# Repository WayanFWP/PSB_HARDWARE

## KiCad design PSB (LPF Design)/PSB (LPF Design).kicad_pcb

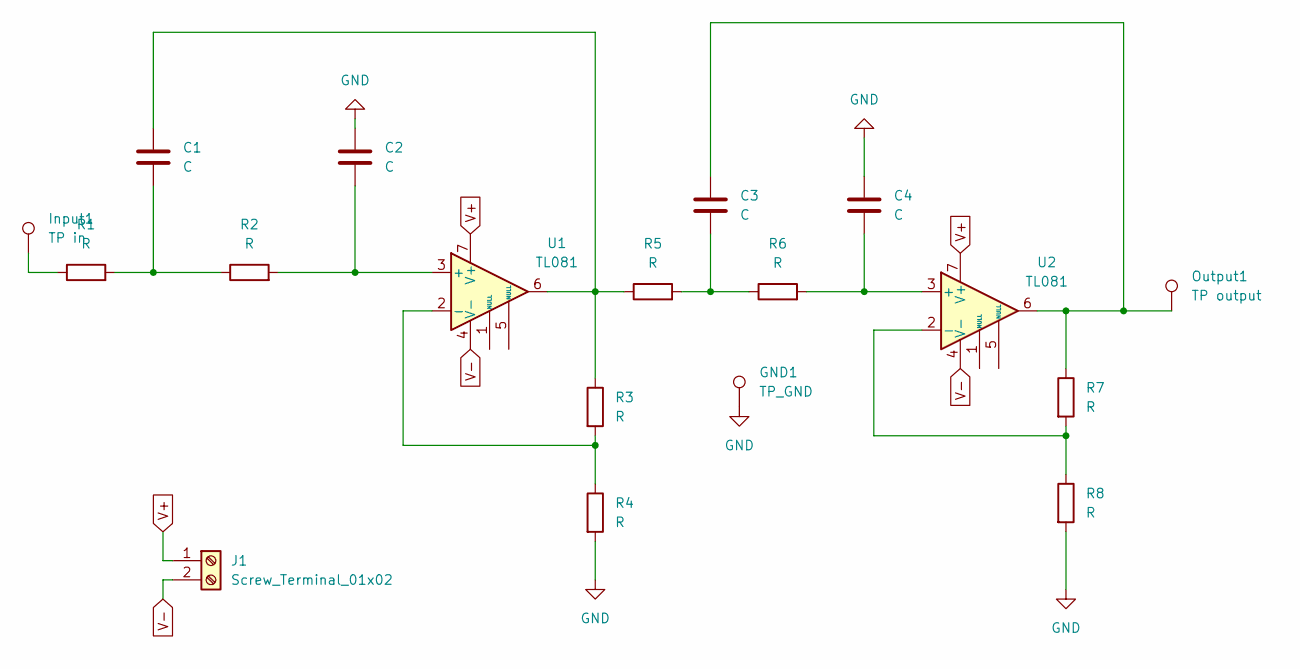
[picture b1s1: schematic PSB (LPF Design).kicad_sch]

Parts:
C1, C2, C3, C4: C; C_Disc_D5.0mm_W2.5mm_P2.50mm
GND1: TP_GND; Pin_D1.3mm_L11.0mm
Input1: TP in; Pin_D1.3mm_L11.0mm
J1: Screw_Terminal_01x02; TerminalBlock_MetzConnect_Type059_RT06302HBWC_1x02_P3.50mm_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
Output1: TP output; Pin_D1.3mm_L11.0mm
R1, R2, R3, R4, R5, R6, R7, R8: R; R_Axial_DIN0207_L6.3mm_D2.5mm_P7.62mm_Horizontal
U1, U2: TL081; DIP-8_W7.62mm_Socket

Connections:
GND: C2.1, C4.1, GND1.1, R4.2, R8.2
unnamed: C1.1, R3.1, R5.1, U1.6
unnamed: C1.2, R1.2, R2.1
unnamed: C3.1, Output1.1, R7.1, U2.6
unnamed: C3.2, R5.2, R6.1
unnamed: Input1.1, R1.1
unnamed: C2.2, R2.2, U1.3 (+)
unnamed: R3.2, R4.1, U1.2 (-)
unnamed: C4.2, R6.2, U2.3 (+)
unnamed: R7.2, R8.1, U2.2 (-)
V+: J1.1, U1.7 (V+), U2.7 (V+); also elsewhere on the board
V-: J1.2, U1.4 (V-), U2.4 (V-); also elsewhere on the board

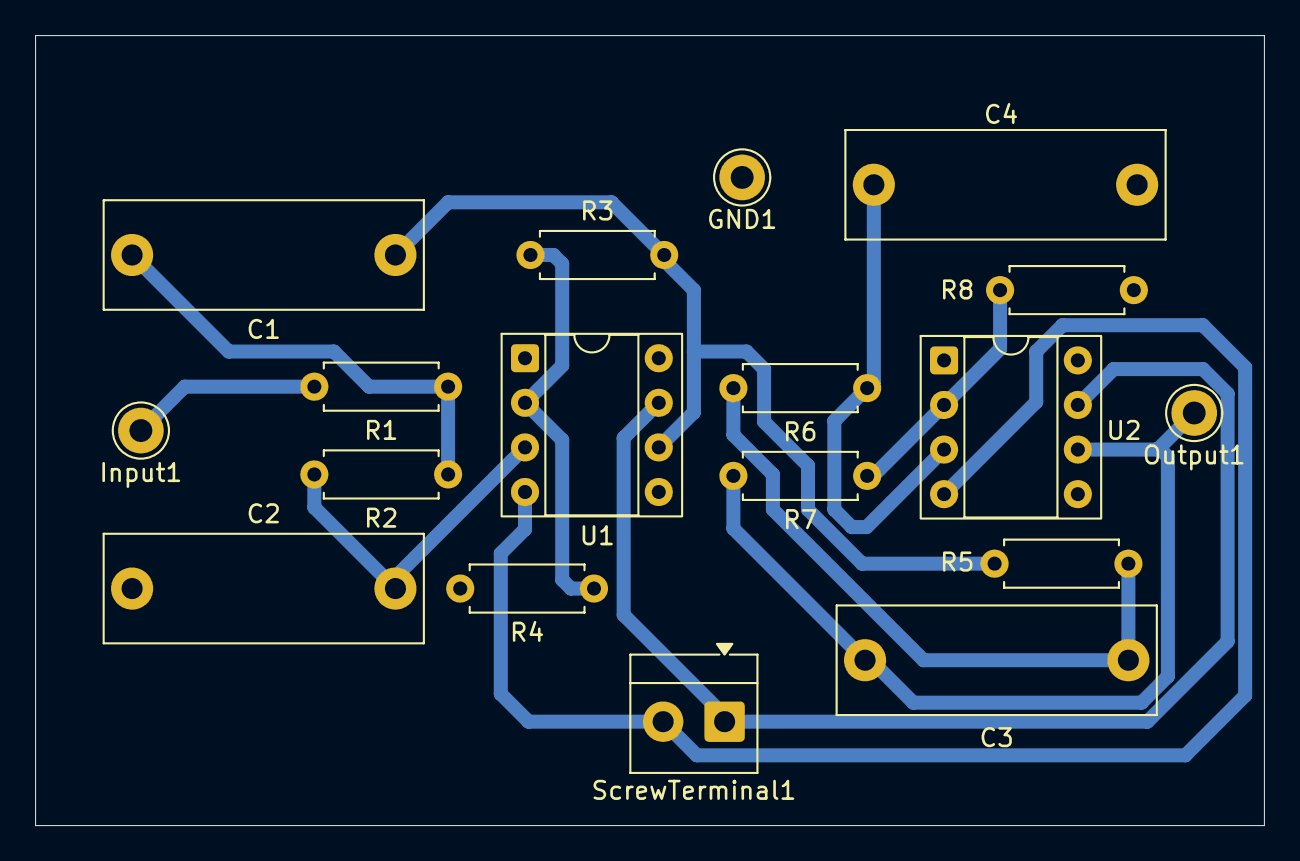
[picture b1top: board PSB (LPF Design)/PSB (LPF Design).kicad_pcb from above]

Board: 2 copper layers, 70.0 x 45.0 mm, 18 parts (0 on the bottom side), 12 nets.

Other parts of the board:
ScrewTerminal1: Screw_Terminal_01x02; TerminalBlock_MetzConnect_Type059_RT06302HBWC_1x02_P3.50mm_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

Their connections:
V+: ScrewTerminal1.1; also elsewhere on the board
V-: ScrewTerminal1.2; also elsewhere on the board

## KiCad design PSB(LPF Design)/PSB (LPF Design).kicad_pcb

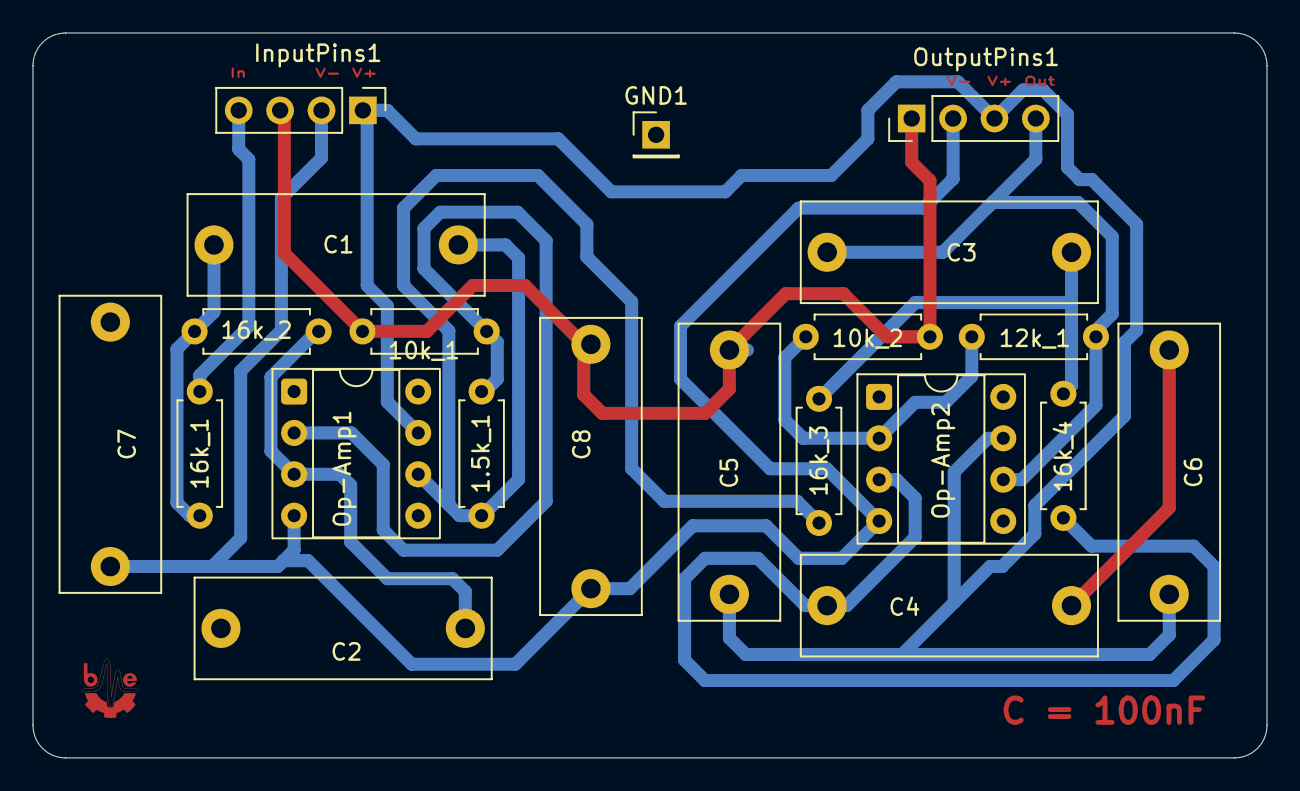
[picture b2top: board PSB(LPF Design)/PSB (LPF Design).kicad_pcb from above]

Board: 2 copper layers, 75.8 x 44.5 mm, 21 parts (0 on the bottom side), 12 nets.

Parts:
1.5k_1, 10k_1, 10k_2, 12k_1, 16k_1, 16k_2, 16k_3, 16k_4: R; R_Axial_DIN0207_L6.3mm_D2.5mm_P7.62mm_Horizontal
C1, C2, C3, C4, C5, C6, C7, C8: C; C_Rect_L18.0mm_W6.0mm_P15.00mm_FKS3_FKP3
GND1: Conn_01x01_Pin; PinHeader_1x01_P2.54mm_Vertical
InputPins1: Conn_01x04_Pin; PinHeader_1x04_P2.54mm_Vertical
Op-Amp1, Op-Amp2: TL081; DIP-8_W7.62mm_Socket
OutputPins1: Conn_01x04_Pin; PinHeader_1x04_P2.54mm_Vertical

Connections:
GND: 10k_1.2, 10k_2.2, C2.1, C4.1, C5.2, C6.2, C7.2, C8.2, GND1.1, InputPins1.3, OutputPins1.1
INPUT: 16k_1.1, InputPins1.4
unnamed: 1.5k_1.1, 16k_3.1, C1.1, Op-Amp1.6
unnamed: 16k_1.2, 16k_2.1, C1.2
unnamed: 16k_4.1, C3.2
unnamed: 16k_2.2, C2.2, Op-Amp1.3 (+)
unnamed: 1.5k_1.2, 10k_1.1, Op-Amp1.2 (-)
unnamed: 16k_4.2, C4.2, Op-Amp2.3 (+)
unnamed: 10k_2.1, 12k_1.2, Op-Amp2.2 (-)
Output: 12k_1.1, C3.1, Op-Amp2.6, OutputPins1.4
V+: C5.1, C6.1, InputPins1.1, Op-Amp1.7 (V+), Op-Amp2.7 (V+), OutputPins1.3
V-: C7.1, C8.1, InputPins1.2, Op-Amp1.4 (V-), Op-Amp2.4 (V-), OutputPins1.2

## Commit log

2025-04-18 LPF design first Commited
2025-04-19 third revision(forgot the resistor)
2025-04-19 reallocate dir sorry
